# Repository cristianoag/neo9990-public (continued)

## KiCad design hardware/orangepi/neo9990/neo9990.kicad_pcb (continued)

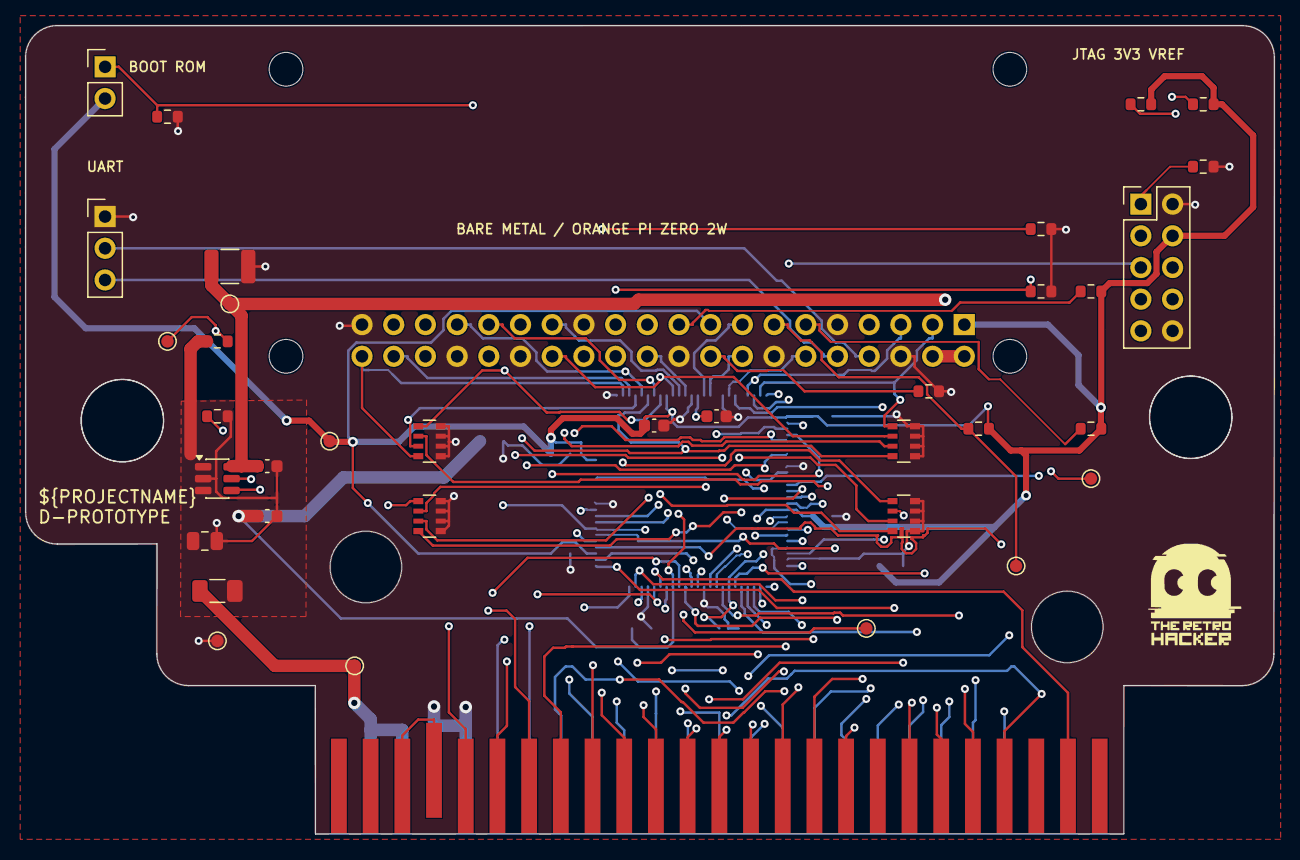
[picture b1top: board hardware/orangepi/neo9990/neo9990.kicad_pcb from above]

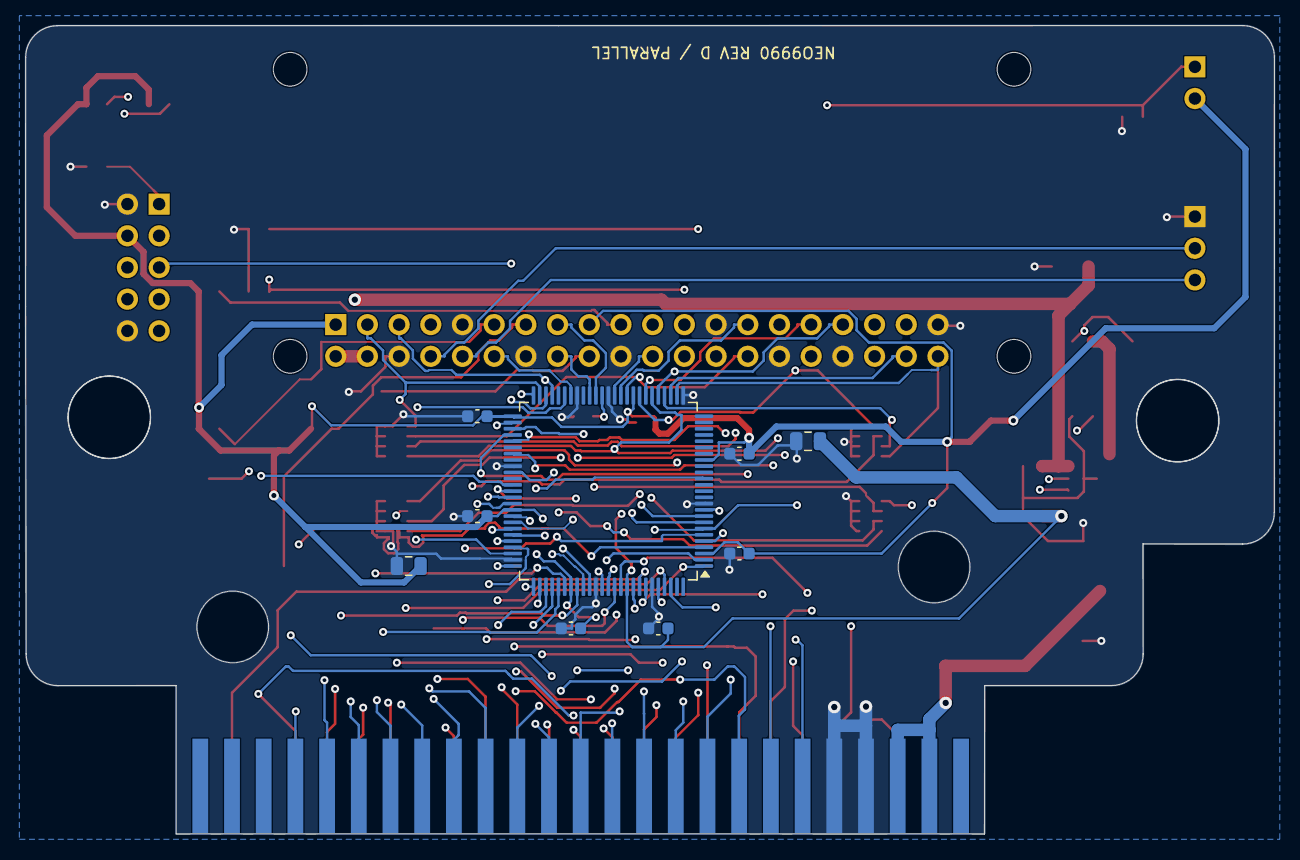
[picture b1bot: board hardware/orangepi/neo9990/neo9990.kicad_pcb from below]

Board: 4 copper layers, 100.1 x 64.8 mm, 50 parts (9 on the bottom side), 75 nets.

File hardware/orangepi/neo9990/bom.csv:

Reference,Value,Footprint,MPN,Description,Side
J1,MSX_CARTRIDGE,neo9990:MSX_Cartridge,,PicoVerse 2040 1.41 original edge geometry and pad sides,F.Cu
J2,ORANGE_PI_ZERO_2W,neo9990:OrangePi_Zero2W,,Socketed above carrier; verify nominal mechanics with physical module,F.Cu
U1,EPM7160STC100-10,Package_QFP:TQFP-100_14x14mm_P0.5mm,EPM7160STC100-10,"MAX7000S back side; VCCINT=5 V, VCCIO=Pi 3.3 V; vendor fitting required",B.Cu
J4,ALTERA_JTAG_3V3_VREF,Connector_PinHeader_2.54mm:PinHeader_2x05_P2.54mm_Vertical,,Altera 2x5 pinout; 3.3 V Vref from Pi; both CPLD rails required,F.Cu
J5,BOOT_ROM_ENABLE,Connector_PinHeader_2.54mm:PinHeader_1x02_P2.54mm_Vertical,,Jumper installed: hold first ROM access until Pi BIOS is ready; power-off changes only,F.Cu
U5,TPS2553DBVR,Package_TO_SOT_SMD:SOT-23-6,TPS2553DBVR,"Soft start, reverse-voltage protection, adjustable current limit",F.Cu
F1,2A_FAST,Fuse:Fuse_1206_3216Metric,0467002.NR,Littelfuse 467; host must independently support stated 2 A,F.Cu
R1,16.9k 1%,Resistor_SMD:R_0603_1608Metric,,,F.Cu
R2,10k,Resistor_SMD:R_0603_1608Metric,,,F.Cu
R3,10k,Resistor_SMD:R_0603_1608Metric,,,F.Cu
R4,10k,Resistor_SMD:R_0603_1608Metric,,,F.Cu
R5,10k,Resistor_SMD:R_0603_1608Metric,,,F.Cu
R6,10k,Resistor_SMD:R_0603_1608Metric,,,F.Cu
R7,10k,Resistor_SMD:R_0603_1608Metric,,,F.Cu
R8,10k,Resistor_SMD:R_0603_1608Metric,,,F.Cu
R9,10k,Resistor_SMD:R_0603_1608Metric,,,F.Cu
R10,10k,Resistor_SMD:R_0603_1608Metric,,,F.Cu
R11,10k,Resistor_SMD:R_0603_1608Metric,,,F.Cu
R12,10k,Resistor_SMD:R_0603_1608Metric,,,F.Cu
RP1,4x100k_ISOLATED,Resistor_SMD:R_Array_Convex_4x0603,,Four isolated 100k pulldowns; defined idle level for host data bus,F.Cu
RP2,4x100k_ISOLATED,Resistor_SMD:R_Array_Convex_4x0603,,Four isolated 100k pulldowns; defined idle level for host data bus,F.Cu
RP3,4x100k_ISOLATED,Resistor_SMD:R_Array_Convex_4x0603,,Four isolated 100k pulldowns; defined idle level for host data bus,F.Cu
RP4,4x100k_ISOLATED,Resistor_SMD:R_Array_Convex_4x0603,,Four isolated 100k pulldowns; defined idle level for host data bus,F.Cu
C1,10u 16V,Capacitor_SMD:C_0805_2012Metric,,,F.Cu
C2,100n 16V,Capacitor_SMD:C_0603_1608Metric,,,F.Cu
C3,47u 10V,Capacitor_SMD:C_1210_3225Metric,,,F.Cu
C4,100n 16V,Capacitor_SMD:C_0603_1608Metric,,,F.Cu
C5,100n 16V,Capacitor_SMD:C_0603_1608Metric,,,F.Cu
C6,100n 16V,Capacitor_SMD:C_0603_1608Metric,,,B.Cu
C7,100n 16V,Capacitor_SMD:C_0603_1608Metric,,,B.Cu
C8,100n 16V,Capacitor_SMD:C_0603_1608Metric,,,B.Cu
C9,100n 16V,Capacitor_SMD:C_0603_1608Metric,,,F.Cu
C10,100n 16V,Capacitor_SMD:C_0603_1608Metric,,,B.Cu
C11,100n 16V,Capacitor_SMD:C_0603_1608Metric,,,B.Cu
C12,100n 16V,Capacitor_SMD:C_0603_1608Metric,,,B.Cu
C13,4.7u 16V,Capacitor_SMD:C_0805_2012Metric,,,B.Cu
C14,4.7u 10V,Capacitor_SMD:C_0805_2012Metric,,,B.Cu
J3,UART0_3V3,Connector_PinHeader_2.54mm:PinHeader_1x03_P2.54mm_Vertical,,,F.Cu
TP1,+5V_SLOT,TestPoint:TestPoint_Pad_D1.0mm,,,F.Cu
TP2,+5V_OPI,TestPoint:TestPoint_Pad_D1.0mm,,,F.Cu
TP3,+3V3_OPI,TestPoint:TestPoint_Pad_D1.0mm,,,F.Cu
TP4,GND,TestPoint:TestPoint_Pad_D1.0mm,,,F.Cu
TP5,HOST_REQUEST,TestPoint:TestPoint_Pad_D1.0mm,,,F.Cu
TP6,HOST_READY,TestPoint:TestPoint_Pad_D1.0mm,,,F.Cu
TP7,HOST_WR_N,TestPoint:TestPoint_Pad_D1.0mm,,,F.Cu
TP8,PWR_FAULT_N,TestPoint:TestPoint_Pad_D1.0mm,,,F.Cu
H1,M2_4mm_OD_STANDOFF,neo9990:ModuleStandoff,,"2.7 mm hole; M2 insulated hardware, spacer OD <= 4 mm, height >= 8 mm",F.Cu
H2,M2_4mm_OD_STANDOFF,neo9990:ModuleStandoff,,"2.7 mm hole; M2 insulated hardware, spacer OD <= 4 mm, height >= 8 mm",F.Cu
H3,M2_4mm_OD_STANDOFF,neo9990:ModuleStandoff,,"2.7 mm hole; M2 insulated hardware, spacer OD <= 4 mm, height >= 8 mm",F.Cu
H4,M2_4mm_OD_STANDOFF,neo9990:ModuleStandoff,,"2.7 mm hole; M2 insulated hardware, spacer OD <= 4 mm, height >= 8 mm",F.Cu

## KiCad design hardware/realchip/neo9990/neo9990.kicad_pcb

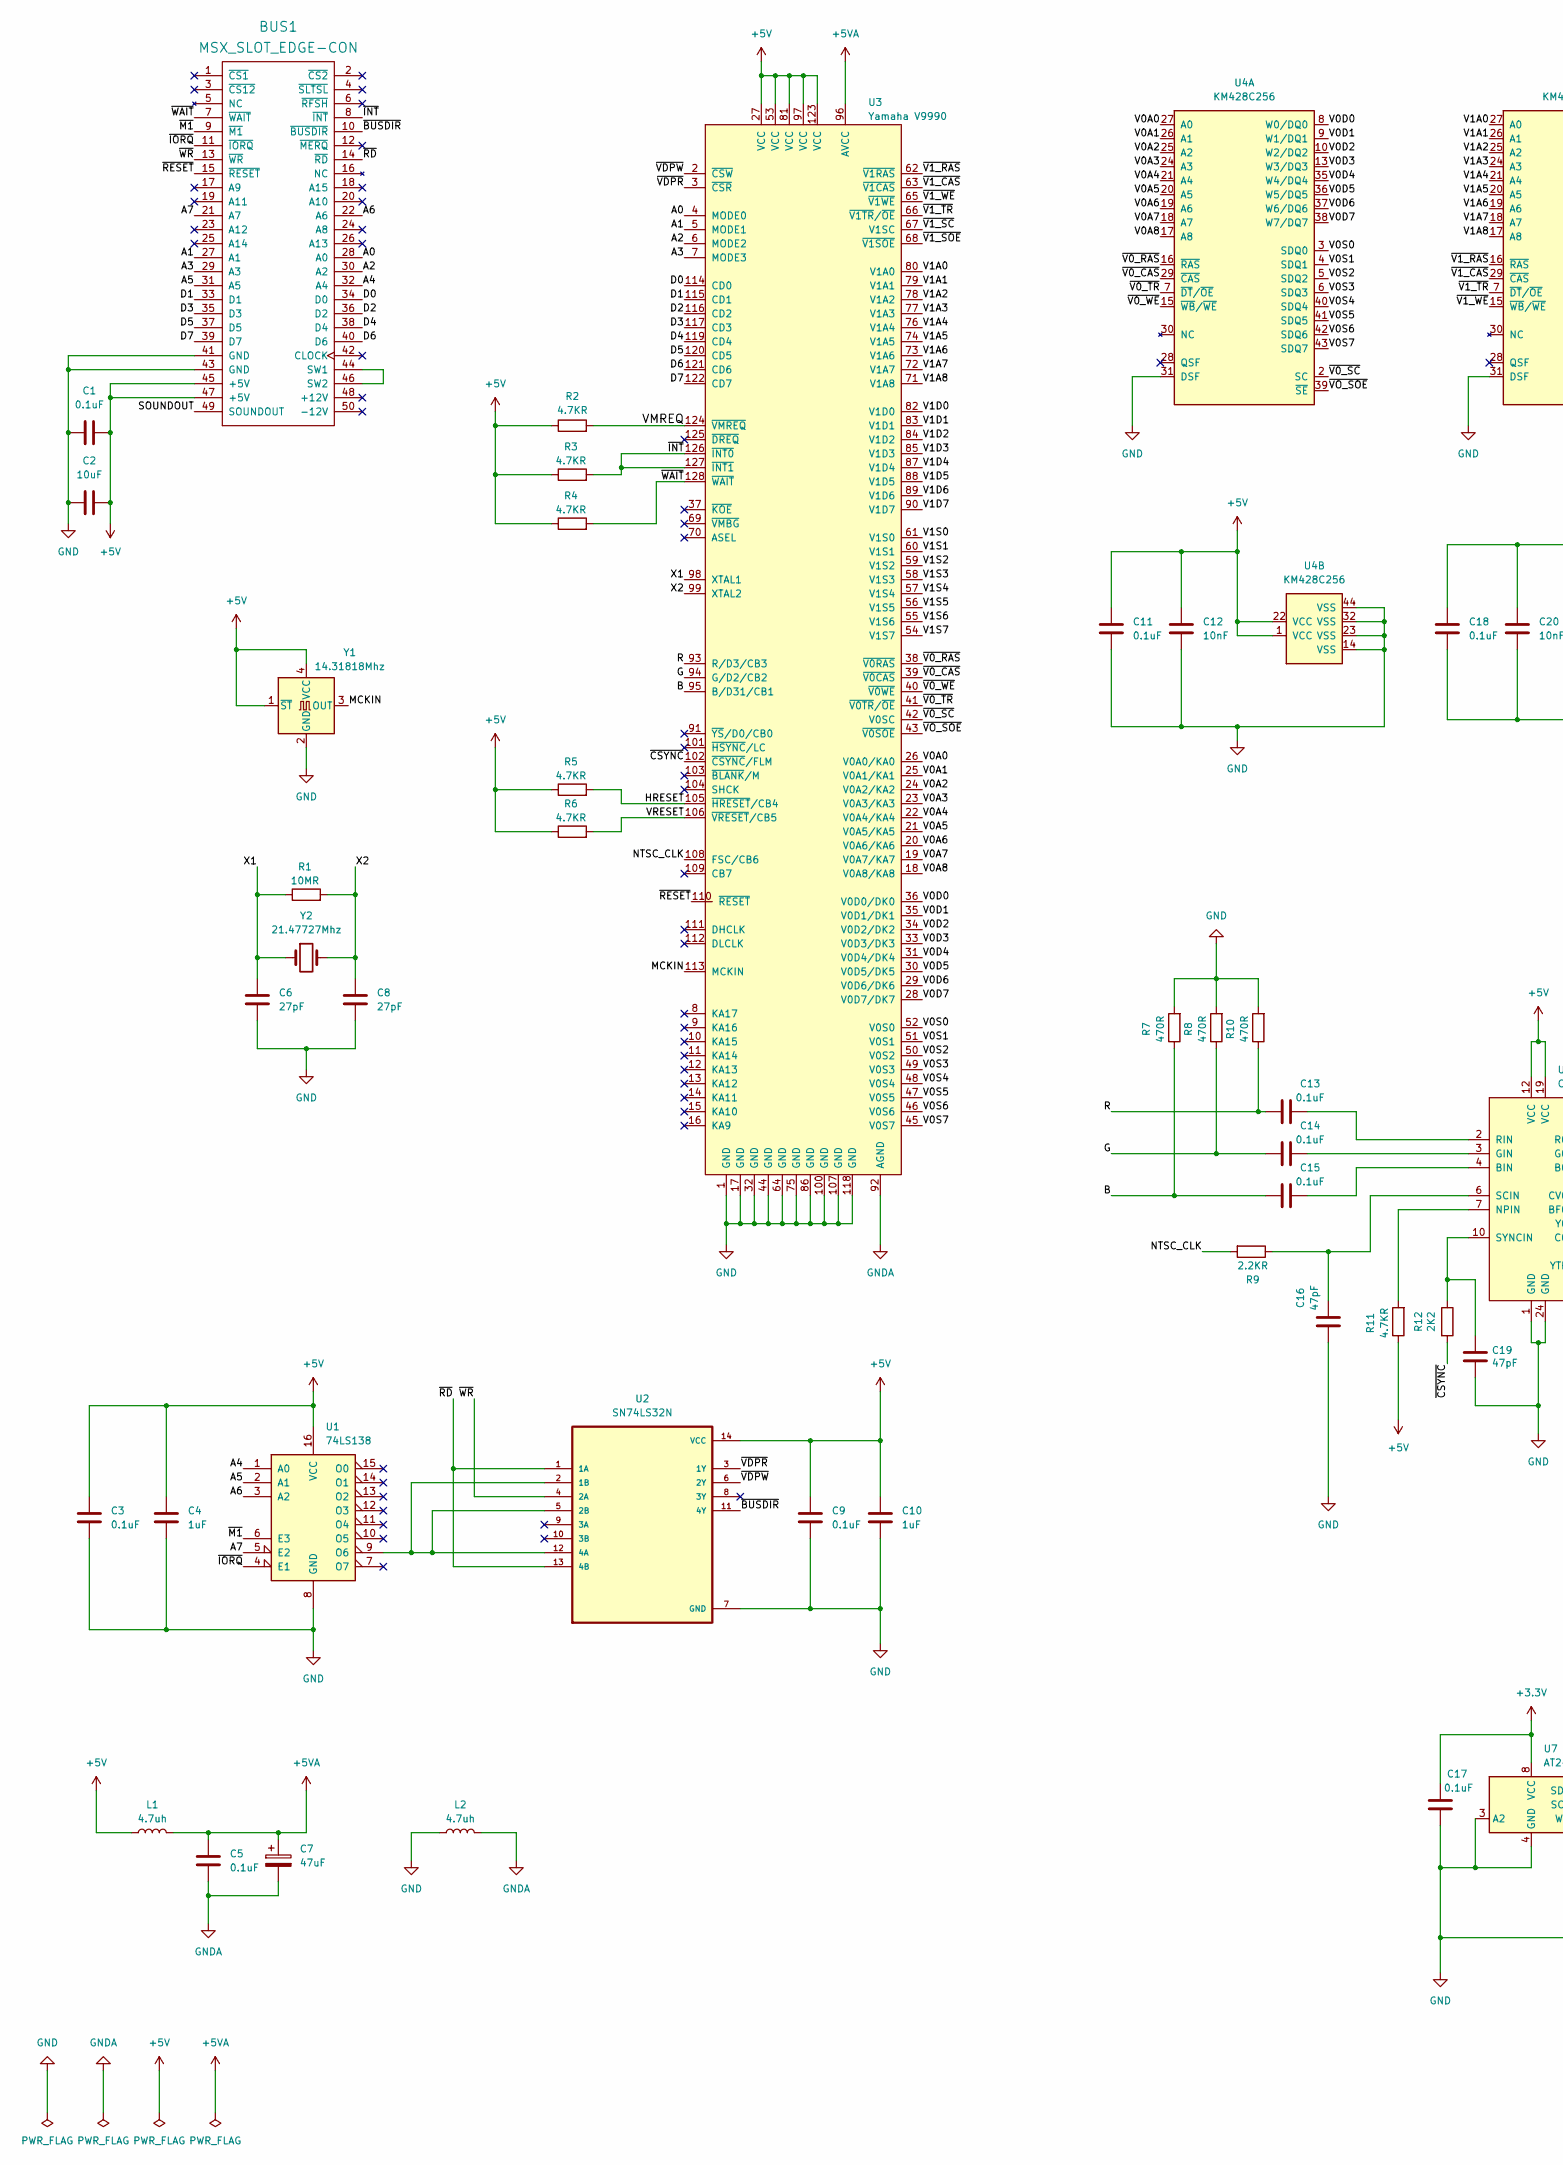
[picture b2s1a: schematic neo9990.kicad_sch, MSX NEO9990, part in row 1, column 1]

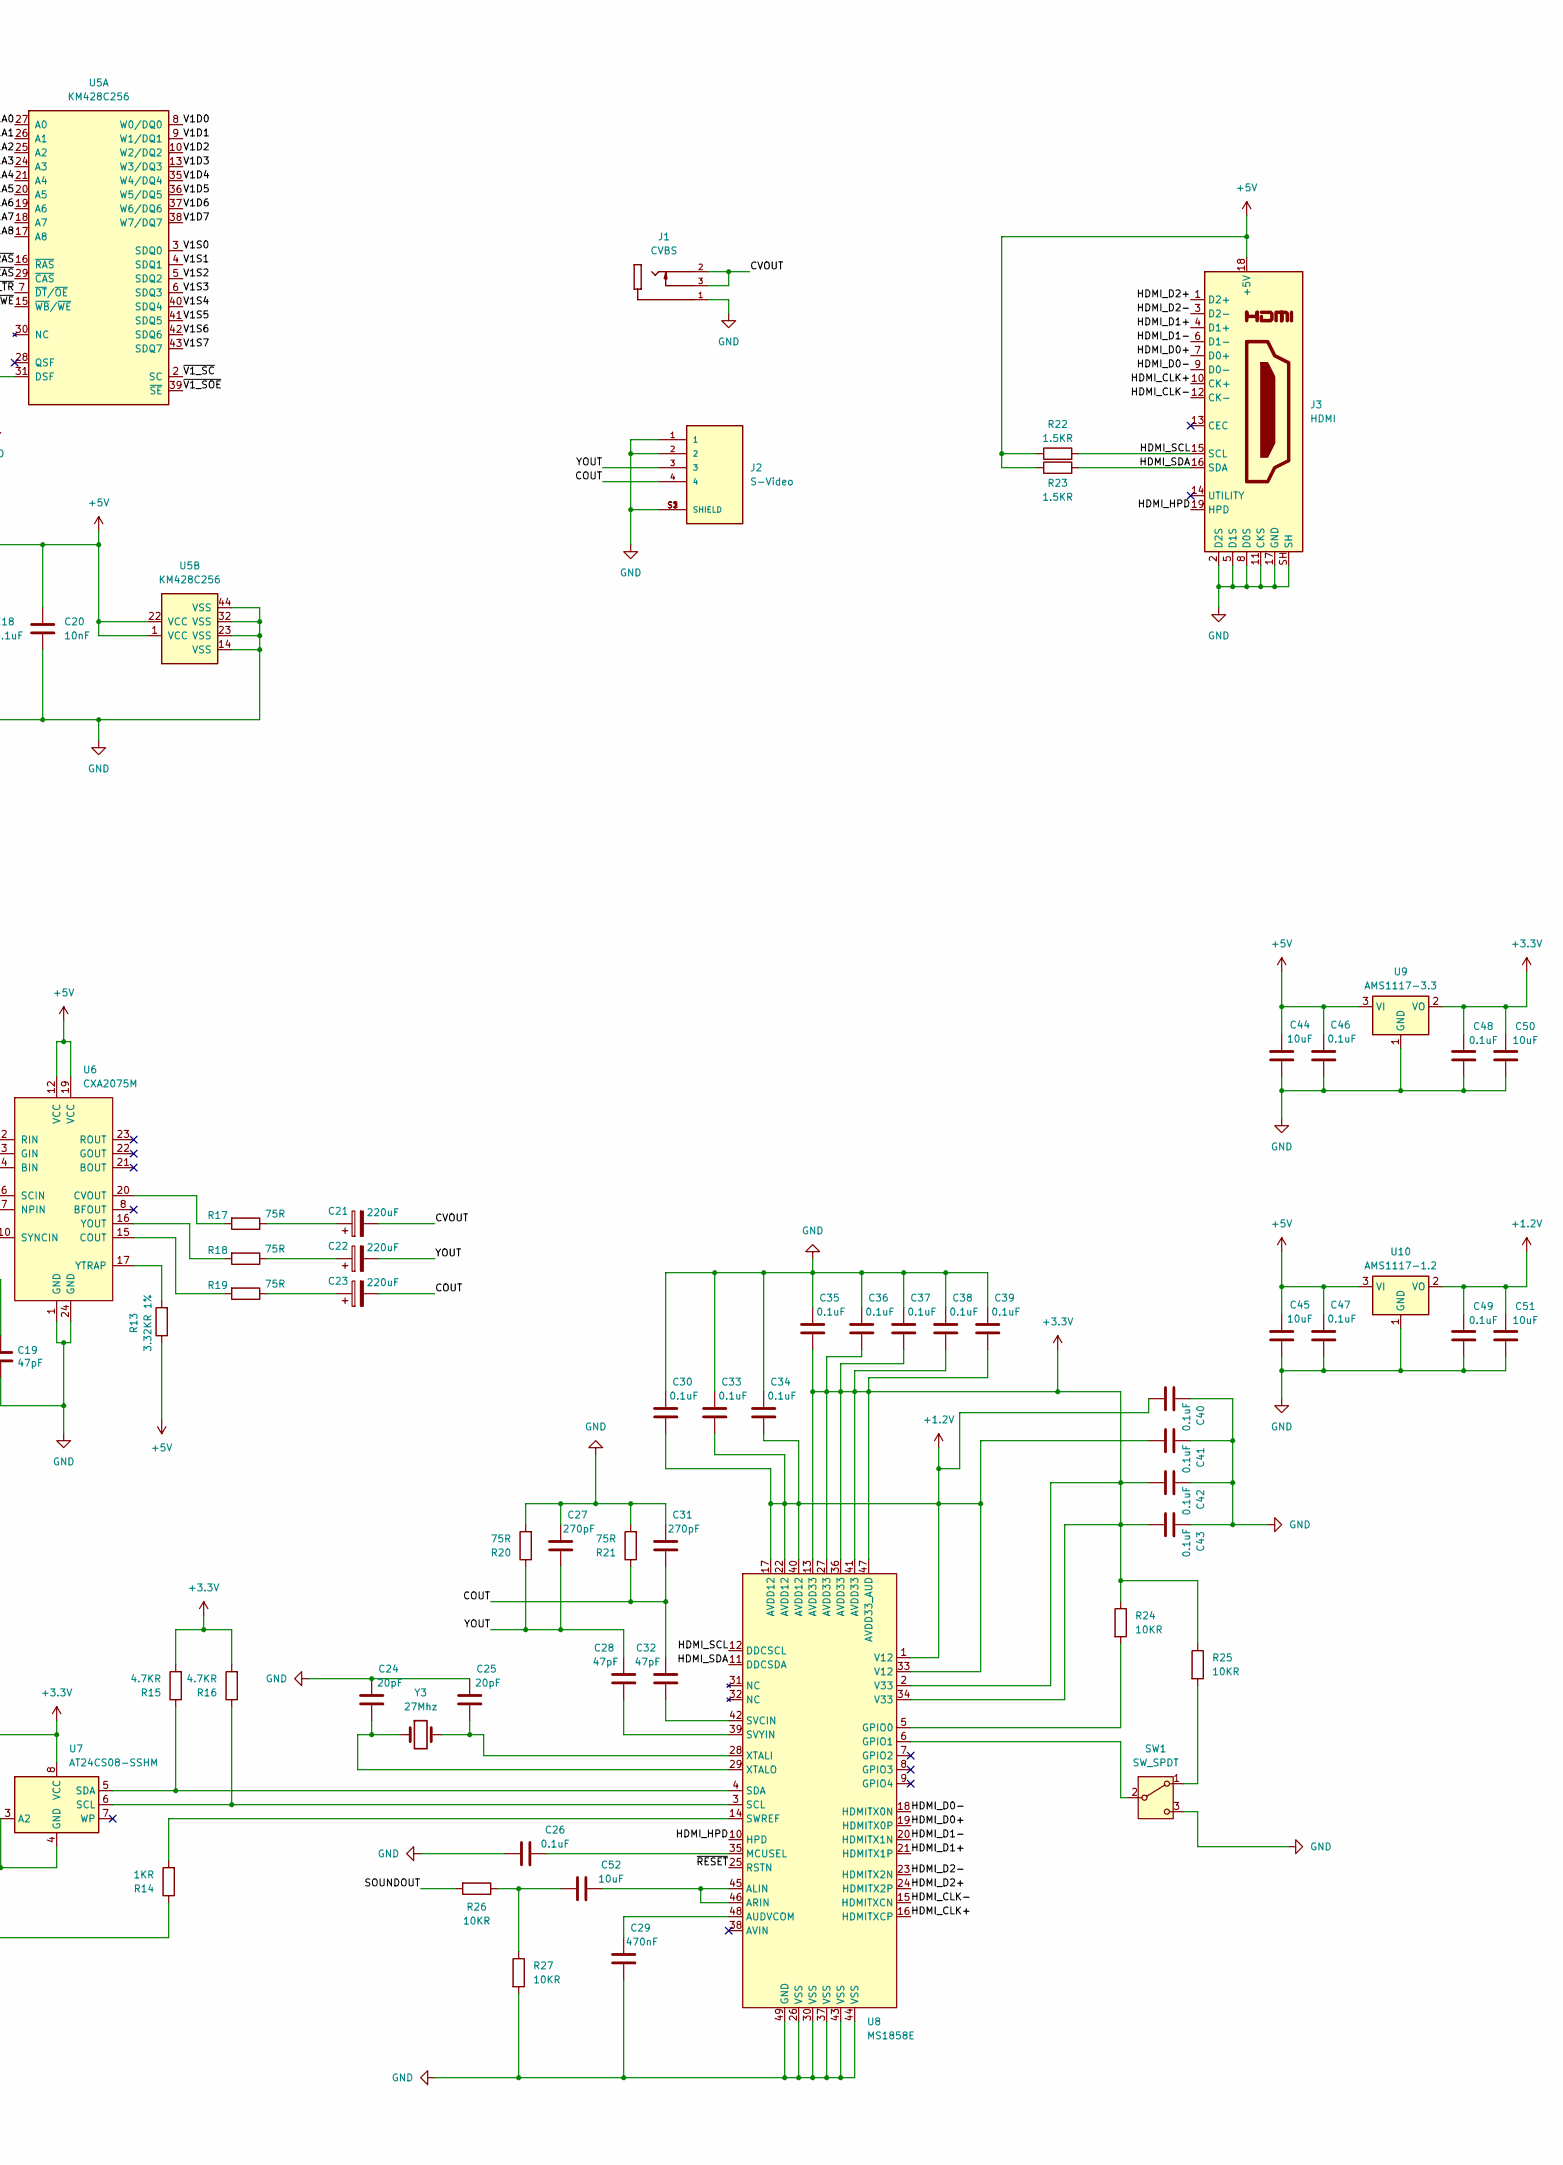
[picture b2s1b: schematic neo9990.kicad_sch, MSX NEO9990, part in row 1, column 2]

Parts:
BUS1: MSX_SLOT_EDGE-CON; msx_cartridge; MPN n/a
C1, C3, C5, C9, C11, C13, C14, C15, C17, C18, C26, C30, C33, C34, C35, C36, C37, C38, C39, C40, C41, C42, C43, C46, C47, C48, C49: 0.1uF; C_0603_1608Metric_Pad1.08x0.95mm_HandSolder
C2, C44, C45, C50, C51, C52: 10uF; C_0603_1608Metric_Pad1.08x0.95mm_HandSolder
C4, C10: 1uF; C_0603_1608Metric_Pad1.08x0.95mm_HandSolder
C6, C8: 27pF; C_0603_1608Metric_Pad1.08x0.95mm_HandSolder
C7: 47uF; C_0603_1608Metric_Pad1.08x0.95mm_HandSolder
C12, C20: 10nF; C_0603_1608Metric_Pad1.08x0.95mm_HandSolder
C16, C19, C28, C32: 47pF; C_0603_1608Metric_Pad1.08x0.95mm_HandSolder
C21, C22, C23: 220uF; CP_EIA-6032-28_Kemet-C_HandSolder
C24, C25: 20pF; C_0603_1608Metric_Pad1.08x0.95mm_HandSolder
C27, C31: 270pF; C_0603_1608Metric_Pad1.08x0.95mm_HandSolder
C29: 470nF; C_0603_1608Metric_Pad1.08x0.95mm_HandSolder
J1: CVBS; SWITCHCRAFT_PJRAN1X1U02AUX; PARTREV A
J2: S-Video; CUI_MD-40SM; PARTREV 02/18/2022
J3: HDMI; TE_1747981-2
L1, L2: 4.7uh; L_0805_2012Metric
R1: 10MR; R_0603_1608Metric_Pad0.98x0.95mm_HandSolder
R2, R3, R4, R5, R6, R11, R15, R16: 4.7KR; R_0603_1608Metric_Pad0.98x0.95mm_HandSolder
R7, R8, R10: 470R; R_0603_1608Metric_Pad0.98x0.95mm_HandSolder
R9: 2.2KR; R_0603_1608Metric_Pad0.98x0.95mm_HandSolder
R12: 2K2; R_0603_1608Metric_Pad0.98x0.95mm_HandSolder
R13: 3.32KR 1%; R_0603_1608Metric_Pad0.98x0.95mm_HandSolder
R14: 1KR; R_0603_1608Metric_Pad0.98x0.95mm_HandSolder
R17, R18, R19, R20, R21: 75R; R_0603_1608Metric_Pad0.98x0.95mm_HandSolder
R22, R23: 1.5KR; R_0603_1608Metric_Pad0.98x0.95mm_HandSolder
R24, R25, R26, R27: 10KR; R_0603_1608Metric_Pad0.98x0.95mm_HandSolder
SW1: SW_SPDT; SK12D07VG4
U1: 74LS138; SOIC-16_3.9x9.9mm_P1.27mm
U2: SN74LS32N; SOIC-14_3.9x8.7mm_P1.27mm
U3: Yamaha V9990; QFP-128_28x28_Pitch0.8mm
U4, U5: KM428C256; TSOP-II-40-44_10.16x18.37mm_P0.8mm
U6: CXA2075M; SOP-24_7.5x15.4mm_P1.27mm
U7: AT24CS08-SSHM; SOIC-8_3.9x4.9mm_P1.27mm
U8: MS1858E; QFN-48-1EP_7x7mm_P0.5mm_EP5.45x5.45mm
U9: AMS1117-3.3; SOT-223-3_TabPin2
U10: AMS1117-1.2; SOT-223-3_TabPin2
Y1: 14.31818Mhz; Crystal_SMD_3225-4Pin_3.2x2.5mm_HandSoldering
Y2: 21.47727Mhz; Crystal_SMD_HC49-SD
Y3: 27Mhz; Crystal_SMD_HC49-SD

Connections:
+1.2V: C30.2, C33.2, C34.2, C40.2, C41.2, C49.2, C51.2, U8.1 (V12), U8.17 (AVDD12), U8.22 (AVDD12), U8.33 (V12), U8.40 (AVDD12), U10.2 (VO)
+3.3V: C17.1, C35.2, C36.2, C37.2, C38.2, C39.2, C42.2, C43.2, C48.2, C50.2, R15.2, R16.2, R24.1, R25.1, U7.8 (VCC), U8.2 (V33), U8.13 (AVDD33), U8.27 (AVDD33), U8.34 (V33), U8.36 (AVDD33), U8.41 (AVDD33), U8.47 (AVDD33_AUD), U9.2 (VO)
+5V: BUS1.45 (+5V), BUS1.47 (+5V), C1.2, C2.2, C3.2, C4.2, C9.1, C10.1, C11.2, C12.2, C18.2, C20.2, C44.1, C45.1, C46.1, C47.1, J3.18 (+5V), L1.1, R2.1, R3.1, R4.1, R5.1, R6.1, R11.1, R13.1, R22.1, R23.1, U1.16 (VCC), U2.14 (VCC), U3.27 (VCC), U3.53 (VCC), U3.81 (VCC), U3.97 (VCC), U3.123 (VCC), U4.1 (VCC), U4.22 (VCC), U5.1 (VCC), U5.22 (VCC), U6.12 (VCC), U6.19 (VCC), U9.3 (VI), U10.3 (VI), Y1.1 (~ST), Y1.4 (VCC)
+5VA: C5.1, C7.1, L1.2, U3.96 (AVCC)
/A0: BUS1.28 (A0), U3.4 (MODE0)
/A1: BUS1.27 (A1), U3.5 (MODE1)
/A2: BUS1.30 (A2), U3.6 (MODE2)
/A3: BUS1.29 (A3), U3.7 (MODE3)
/A4: BUS1.32 (A4), U1.1 (A0)
/A5: BUS1.31 (A5), U1.2 (A1)
/A6: BUS1.22 (A6), U1.3 (A2)
/A7: BUS1.21 (A7), U1.5 (E2)
/B: C15.2, R7.1, U3.95 (B/D31/CB1)
/COUT: C23.2, C31.2, C32.1, J2.4, R21.1
/CVOUT: C21.2, J1.2, J1.3
/D0: BUS1.34 (D0), U3.114 (CD0)
/D1: BUS1.33 (D1), U3.115 (CD1)
/D2: BUS1.36 (D2~), U3.116 (CD2)
/D3: BUS1.35 (D3), U3.117 (CD3)
/D4: BUS1.38 (D4), U3.119 (CD4)
/D5: BUS1.37 (D5), U3.120 (CD5)
/D6: BUS1.40 (D6), U3.121 (CD6)
/D7: BUS1.39 (D7), U3.122 (CD7)
/G: C14.2, R8.1, U3.94 (G/D2/CB2)
/HDMI_CLK+: J3.10 (CK+), U8.16 (HDMITXCP)
/HDMI_CLK-: J3.12 (CK-), U8.15 (HDMITXCN)
/HDMI_D0+: J3.7 (D0+), U8.19 (HDMITX0P)
/HDMI_D0-: J3.9 (D0-), U8.18 (HDMITX0N)
/HDMI_D1+: J3.4 (D1+), U8.21 (HDMITX1P)
/HDMI_D1-: J3.6 (D1-), U8.20 (HDMITX1N)
/HDMI_D2+: J3.1 (D2+), U8.24 (HDMITX2P)
/HDMI_D2-: J3.3 (D2-), U8.23 (HDMITX2N)
/HDMI_HPD: J3.19 (HPD), U8.10 (HPD)
/HDMI_SCL: J3.15 (SCL), R22.2, U8.12 (DDCSCL)
/HDMI_SDA: J3.16 (SDA), R23.2, U8.11 (DDCSDA)
/HRESET: R5.2, U3.105 (~HRESET/CB4)
/MCKIN: U3.113 (MCKIN), Y1.3 (OUT)
/NTSC_CLK: R9.2, U3.108 (FSC/CB6)
/R: C13.2, R10.1, U3.93 (R/D3/CB3)
/SOUNDOUT: BUS1.49 (SOUNDOUT), R26.2
/V0A0: U3.26 (V0A0/KA0), U4.27 (A0)
/V0A1: U3.25 (V0A1/KA1), U4.26 (A1)
/V0A2: U3.24 (V0A2/KA2), U4.25 (A2)
/V0A3: U3.23 (V0A3/KA3), U4.24 (A3)
/V0A4: U3.22 (V0A4/KA4), U4.21 (A4)
/V0A5: U3.21 (V0A5/KA5), U4.20 (A5)
/V0A6: U3.20 (V0A6/KA6), U4.19 (A6)
/V0A7: U3.19 (V0A7/KA7), U4.18 (A7)
/V0A8: U3.18 (V0A8/KA8), U4.17 (A8)
/V0D0: U3.36 (V0D0/DK0), U4.8 (W0/DQ0)
/V0D1: U3.35 (V0D1/DK1), U4.9 (W1/DQ1)
/V0D2: U3.34 (V0D2/DK2), U4.10 (W2/DQ2)
/V0D3: U3.33 (V0D3/DK3), U4.13 (W3/DQ3)
/V0D4: U3.31 (V0D4/DK4), U4.35 (W4/DQ4)
/V0D5: U3.30 (V0D5/DK5), U4.36 (W5/DQ5)
/V0D6: U3.29 (V0D6/DK6), U4.37 (W6/DQ6)
/V0D7: U3.28 (V0D7/DK7), U4.38 (W7/DQ7)
/V0S0: U3.52 (V0S0), U4.3 (SDQ0)
/V0S1: U3.51 (V0S1), U4.4 (SDQ1)
/V0S2: U3.50 (V0S2), U4.5 (SDQ2)
/V0S3: U3.49 (V0S3), U4.6 (SDQ3)
/V0S4: U3.48 (V0S4), U4.40 (SDQ4)
/V0S5: U3.47 (V0S5), U4.41 (SDQ5)
/V0S6: U3.46 (V0S6), U4.42 (SDQ6)
/V0S7: U3.45 (V0S7), U4.43 (SDQ7)
/V1A0: U3.80 (V1A0), U5.27 (A0)
/V1A1: U3.79 (V1A1), U5.26 (A1)
/V1A2: U3.78 (V1A2), U5.25 (A2)
/V1A3: U3.77 (V1A3), U5.24 (A3)
/V1A4: U3.76 (V1A4), U5.21 (A4)
/V1A5: U3.74 (V1A5), U5.20 (A5)
/V1A6: U3.73 (V1A6), U5.19 (A6)
/V1A7: U3.72 (V1A7), U5.18 (A7)
/V1A8: U3.71 (V1A8), U5.17 (A8)
/V1D0: U3.82 (V1D0), U5.8 (W0/DQ0)
/V1D1: U3.83 (V1D1), U5.9 (W1/DQ1)
/V1D2: U3.84 (V1D2), U5.10 (W2/DQ2)
/V1D3: U3.85 (V1D3), U5.13 (W3/DQ3)
/V1D4: U3.87 (V1D4), U5.35 (W4/DQ4)
/V1D5: U3.88 (V1D5), U5.36 (W5/DQ5)
/V1D6: U3.89 (V1D6), U5.37 (W6/DQ6)
/V1D7: U3.90 (V1D7), U5.38 (W7/DQ7)
/V1S0: U3.61 (V1S0), U5.3 (SDQ0)
/V1S1: U3.60 (V1S1), U5.4 (SDQ1)
/V1S2: U3.59 (V1S2), U5.5 (SDQ2)
/V1S3: U3.58 (V1S3), U5.6 (SDQ3)
/V1S4: U3.57 (V1S4), U5.40 (SDQ4)
/V1S5: U3.56 (V1S5), U5.41 (SDQ5)
/V1S6: U3.55 (V1S6), U5.42 (SDQ6)
/V1S7: U3.54 (V1S7), U5.43 (SDQ7)
/VMREQ: R2.2, U3.124 (~VMREQ)
/VRESET: R6.2, U3.106 (~VRESET/CB5)
/X1: C6.1, R1.1, U3.98 (XTAL1), Y2.1
/X2: C8.1, R1.2, U3.99 (XTAL2), Y2.2
/YOUT: C22.2, C27.2, C28.1, J2.3, R20.1
/~BUSDIR: BUS1.10 (~BUSDIR), U2.11 (4Y)
/~CSYNC: R12.2, U3.102 (~CSYNC/FLM)
/~INT: BUS1.8 (~INT), R3.2, U3.126 (~INT0), U3.127 (~INT1)
/~IORQ: BUS1.11 (~IORQ), U1.4 (E1)
/~M1: BUS1.9 (~M1), U1.6 (E3)
/~RD: BUS1.14 (~RD), U2.1 (1A), U2.13 (4B)
/~RESET: BUS1.15 (~RESET), U3.110 (~RESET), U8.25 (RSTN)
/~V0_CAS: U3.39 (~V0CAS), U4.29 (~CAS)
/~V0_RAS: U3.38 (~V0RAS), U4.16 (~RAS)
/~V0_SC: U3.42 (V0SC), U4.2 (SC)
/~V0_TR: U3.41 (~V0TR/~OE), U4.7 (~DT/~OE)
/~V0_WE: U3.40 (~V0WE), U4.15 (~WB/~WE)
/~V1_CAS: U3.63 (~V1CAS), U5.29 (~CAS)
/~V1_RAS: U3.62 (~V1RAS), U5.16 (~RAS)
/~V1_SC: U3.67 (V1SC), U5.2 (SC)
/~V1_SOE: U3.68 (~V1SOE), U5.39 (~SE)
/~V1_TR: U3.66 (~V1TR/~OE), U5.7 (~DT/~OE)
/~V1_WE: U3.65 (~V1WE), U5.15 (~WB/~WE)
/~VDPR: U2.3 (1Y), U3.3 (~CSR)
/~VDPW: U2.6 (2Y), U3.2 (~CSW)
/~VO_SOE: U3.43 (~V0SOE), U4.39 (~SE)
/~WAIT: BUS1.7 (~WAIT), R4.2, U3.128 (~WAIT)
/~WR: BUS1.13 (~WR), U2.4 (2A)
GND: BUS1.41 (GND), BUS1.43 (GND), C1.1, C2.1, C3.1, C4.1, C6.2, C8.2, C9.2, C10.2, C11.1, C12.1, C16.2, C17.2, C18.1, C19.2, C20.1, C24.1, C25.1, C26.1, C27.1, C29.2, C30.1, C31.1, C33.1, C34.1, C35.1, C36.1, C37.1, C38.1, C39.1, C40.1, C41.1, C42.1, C43.1, C44.2, C45.2, C46.2, C47.2, C48.1, C49.1, C50.1, C51.1, J1.1, J2.1, J2.2, J2.S1 (SHIELD), J2.S2 (SHIELD), J2.S3 (SHIELD), J3.2 (D2S), J3.5 (D1S), J3.8 (D0S), J3.11 (CKS), J3.17 (GND), J3.SH, L2.1, R7.2, R8.2, R10.2, R14.1, R20.2, R21.2, R27.2, SW1.3 (C), U1.8 (GND), U2.7 (GND), U3.1 (GND), U3.17 (GND), U3.32 (GND), U3.44 (GND), U3.64 (GND), U3.75 (GND), U3.86 (GND), U3.100 (GND), U3.107 (GND), U3.118 (GND), U4.14 (VSS), U4.23 (VSS), U4.31 (DSF), U4.32 (VSS), U4.44 (VSS), U5.14 (VSS), U5.23 (VSS), U5.31 (DSF), U5.32 (VSS), U5.44 (VSS), U6.1 (GND), U6.24 (GND), U7.3 (A2), U7.4 (GND), U8.26 (VSS), U8.30 (VSS), U8.37 (VSS), U8.43 (VSS), U8.44 (VSS), U8.49 (GND), U9.1 (GND), U10.1 (GND), Y1.2 (GND)
GNDA: C5.2, C7.2, L2.2, U3.92 (AGND)
unnamed: BUS1.44 (SW1), BUS1.46 (SW2)
unnamed: C21.1, R17.1
unnamed: C22.1, R18.1
unnamed: C23.1, R19.1
unnamed: C52.1, R26.1, R27.1
unnamed: R25.2, SW1.1 (A)
unnamed: SW1.2 (B), U8.6 (GPIO1)
unnamed: U1.9 (O6), U2.2 (1B), U2.5 (2B), U2.12 (4A)
unnamed: C15.1, U6.4 (BIN)
unnamed: R19.2, U6.15 (COUT)
unnamed: R17.2, U6.20 (CVOUT)
unnamed: C14.1, U6.3 (GIN)
unnamed: R11.2, U6.7 (NPIN)
unnamed: C13.1, U6.2 (RIN)
unnamed: C16.1, R9.1, U6.6 (SCIN)
unnamed: C19.1, R12.1, U6.10 (SYNCIN)
unnamed: R18.2, U6.16 (YOUT)
unnamed: R13.2, U6.17 (YTRAP)
unnamed: R16.1, U7.6 (SCL), U8.3 (SCL)
unnamed: R15.1, U7.5 (SDA), U8.4 (SDA)
unnamed: C52.2, U8.45 (ALIN), U8.46 (ARIN)
unnamed: C29.1, U8.48 (AUDVCOM)
unnamed: R24.2, U8.5 (GPIO0)
unnamed: C26.2, U8.35 (MCUSEL)
unnamed: C32.2, U8.42 (SVCIN)
unnamed: C28.2, U8.39 (SVYIN)
unnamed: R14.2, U8.14 (SWREF)
unnamed: C25.2, U8.28 (XTALI), Y3.2
unnamed: C24.2, U8.29 (XTALO), Y3.1

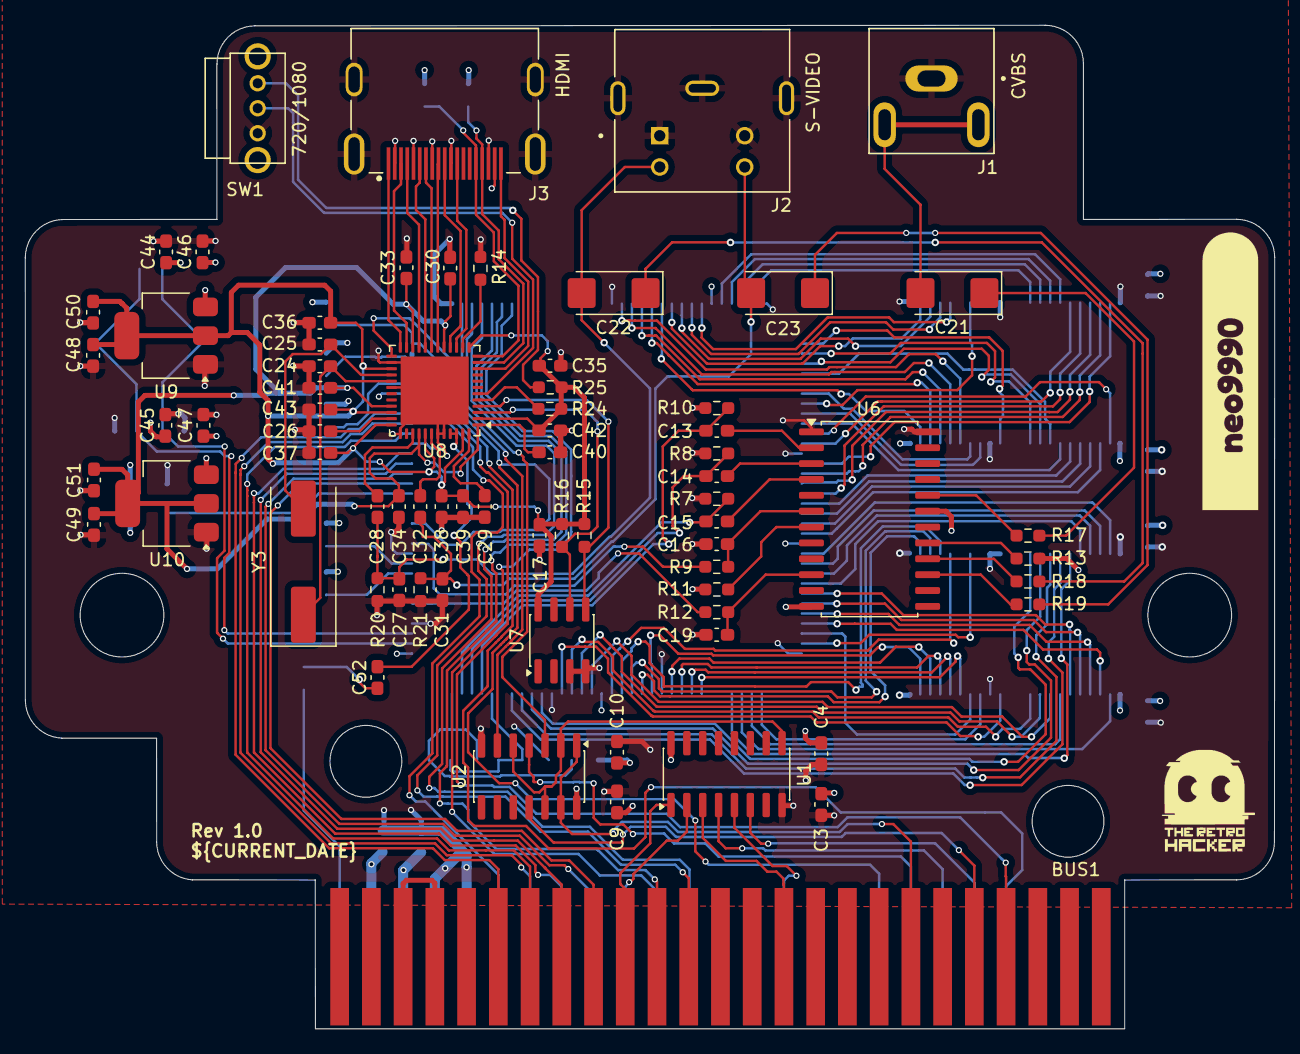
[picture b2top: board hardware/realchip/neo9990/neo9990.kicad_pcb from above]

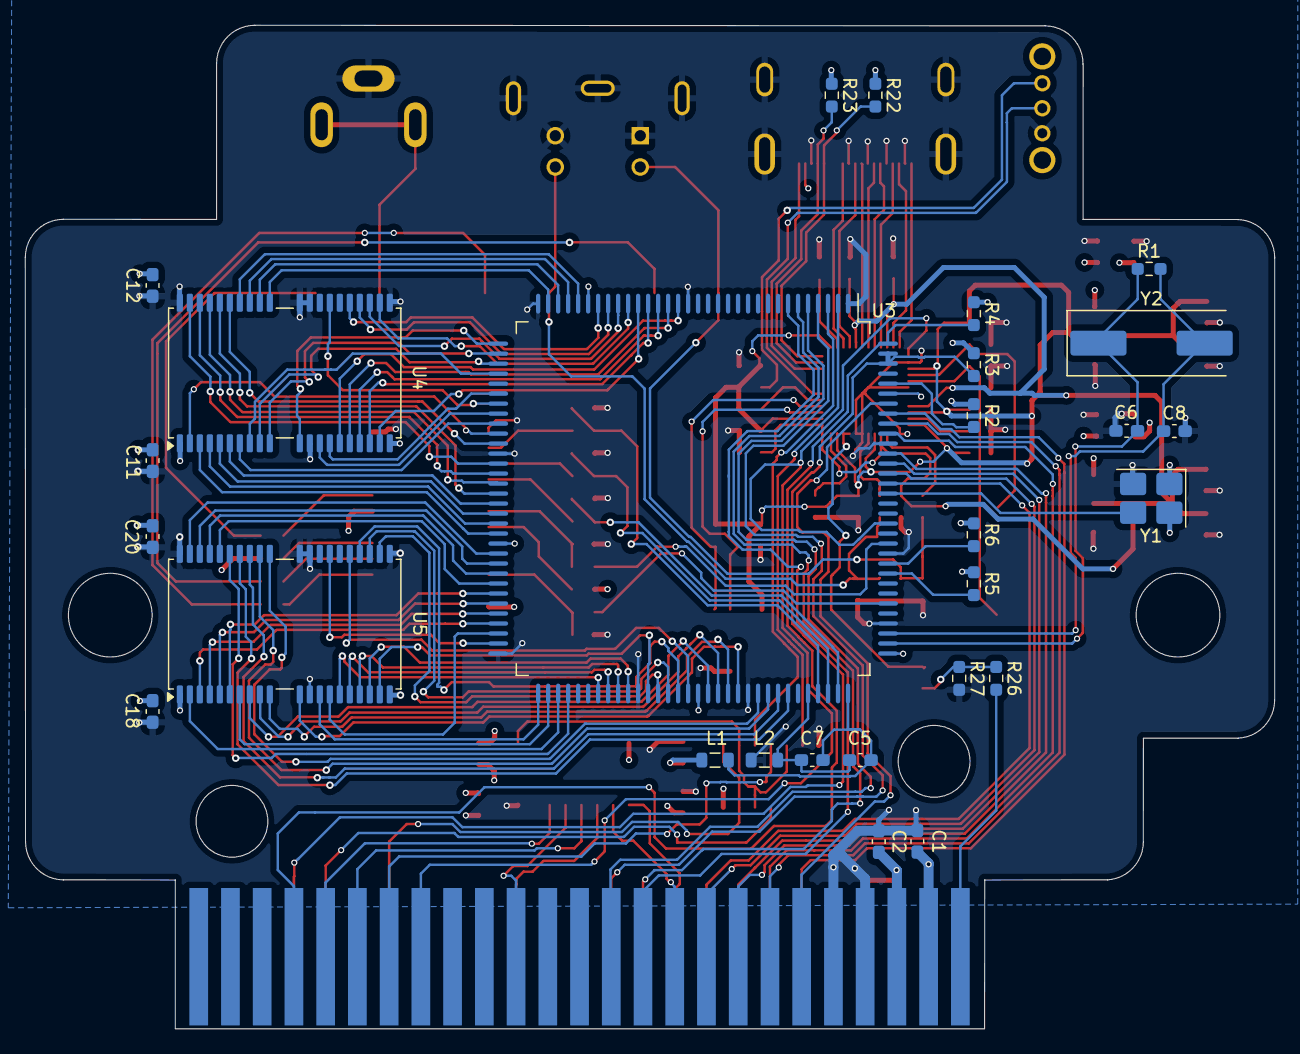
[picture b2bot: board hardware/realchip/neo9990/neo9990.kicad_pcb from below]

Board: 4 copper layers, 100.0 x 80.3 mm, 100 parts (27 on the bottom side), 149 nets.

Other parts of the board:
kibuzzard-68E299D1: G***; kibuzzard-68E299D1

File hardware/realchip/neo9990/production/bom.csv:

Designator,Footprint,Quantity,Value,LCSC Part #
"C1, C11, C13, C14, C15, C17, C18, C26, C3, C30, C33, C34, C35, C36, C37, C38, C39, C40, C41, C42, C43, C46, C47, C48, C49, C5, C9",0603,27,0.1uF,
"C10, C4",0603,2,1uF,
"C12, C20",0603,2,10nF,
"C16, C19, C28, C32",0603,4,47pF,
"C2, C44, C45, C50, C51, C52",0603,6,10uF,
"C21, C22, C23",CP_EIA-6032-28_Kemet-C_HandSolder,3,220uF,
"C24, C25",0603,2,20pF,
"C27, C31",0603,2,270pF,
C29,0603,1,470nF,
"C6, C8",0603,2,27pF,
C7,0603,1,47uF,
J1,SWITCHCRAFT_PJRAN1X1U02AUX,1,CVBS,
J2,CUI_MD-40SM,1,S-Video,
J3,TE_1747981-2,1,HDMI,
"L1, L2",0805,2,4.7uh,
R1,0603,1,10MR,
"R10, R7, R8",0603,3,470R,
"R11, R15, R16, R2, R3, R4, R5, R6",0603,8,4.7KR,
R12,0603,1,2K2,
R13,0603,1,3.32KR 1%,
R14,0603,1,1KR,
"R17, R18, R19, R20, R21",0603,5,75R,
"R22, R23",0603,2,1.5KR,
"R24, R25, R26, R27",0603,4,10KR,
R9,0603,1,2.2KR,
SW1,SK12D07VG4,1,SW_SPDT,
U1,SOIC-16_3.9x9.9mm_P1.27mm,1,74LS138,
U10,SOT-223-3_TabPin2,1,AMS1117-1.2,
U2,SOIC-14_3.9x8.7mm_P1.27mm,1,SN74LS32N,
U3,QFP-128_28x28_Pitch0.8mm,1,Yamaha V9990,
"U4, U5",TSOP-II-40-44_10.16x18.37mm_P0.8mm,2,KM428C256,
U6,SOP-24_7.5x15.4mm_P1.27mm,1,CXA2075M,
U7,SOIC-8_3.9x4.9mm_P1.27mm,1,AT24CS08-SSHM,
U8,QFN-48-1EP_7x7mm_P0.5mm_EP5.45x5.45mm,1,MS1858E,
U9,SOT-223-3_TabPin2,1,AMS1117-3.3,
Y1,Crystal_SMD_3225-4Pin_3.2x2.5mm_HandSoldering,1,14.31818Mhz,
Y2,Crystal_SMD_HC49-SD,1,21.47727Mhz,
Y3,Crystal_SMD_HC49-SD,1,27Mhz,
